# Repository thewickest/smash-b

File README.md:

# Smashboard
Ortholinear bluetooth split keyboard.

Just another split keyboard. Developed with KiKad7.0 and Fusion360.

ZMK configuration in [Smashboard-config](https://github.com/thewickest/smashboard-config)

# Features
- Powered by nice!nano microcontroller
- Compatible with nice!view OLED screen
- Hotswap for MX style Switches
- Different types of cases
- ZMK
- VIA Support
- Bluetooth

# Assembly
Parts needed. I will be linking the parts that I used. Feel free to use other parts, specially for the switches and the hotswap sockets. You can also change the remaining parts but you will have to modify the PCB most probably.
- 2x nice!nano
- 2x nice!view (optional)
- 44x MX Style switches
- 44x Hotswap sockets
- 48x Millmax sockets
- 10x millmax headers sockets
- 2x JST Battery connector (optional)
- 2x Power off/on switch
- 2x Reset button

# Roadmap
- [ ] Hotswap for low profile switches
- [x] Shell case

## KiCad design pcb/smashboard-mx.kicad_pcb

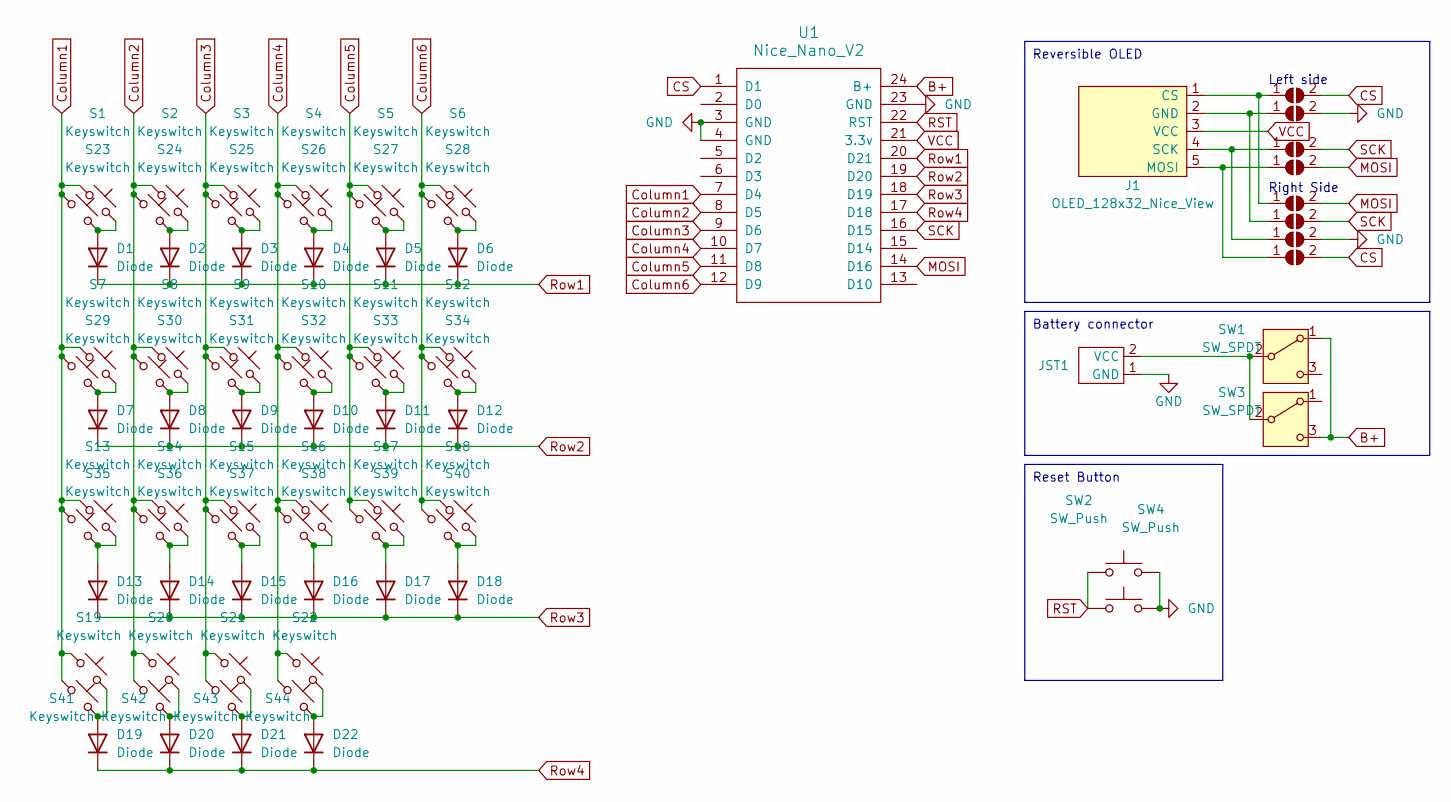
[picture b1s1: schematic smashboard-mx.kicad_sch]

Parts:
D1, D2, D3, D4, D5, D6, D7, D8, D9, D10, D11, D12, D13, D14, D15, D16, D17, D18, D19, D20, D21, D22: Diode; Diode_DO-35
J1: OLED_128x32_Nice_View
JP1, JP2, JP4, JP5, JP6, JP7, JP9, JP10: SolderJumper_2_Open; SolderJumper-2_P1.3mm_Open_TrianglePad1.0x1.5mm
JST1: JST_PH_S2B-PH-K_1x02_P2.00mm_Horizontal
S1, S2, S3, S4, S5, S6, S7, S8, S9, S10, S11, S12, S13, S14, S15, S16, S17, S18, S19, S20, S21, S22, S23, S24, S25, S26, S27, S28, S29, S30, S31, S32, S33, S34, S35, S36, S37, S38, S39, S40, S41, S42, S43, S44: Keyswitch; Hotswap_MX
SW1, SW3: SW_SPDT; SW_SPDT_PCM12
SW2, SW4: SW_Push; Panasonic_EVQPUK_EVQPUB
U1: Nice_Nano_V2

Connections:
B+: SW1.1 (A), SW3.3 (C), U1.24 (B+)
CS: JP1.2 (B), JP10.2 (B), U1.1 (D1)
Column1: S1.1, S7.1, S13.1, S19.1, S23.1, S29.1, S35.1, S41.1, U1.7 (D4)
Column2: S2.1, S8.1, S14.1, S20.1, S24.1, S30.1, S36.1, S42.1, U1.8 (D5)
Column3: S3.1, S9.1, S15.1, S21.1, S25.1, S31.1, S37.1, S43.1, U1.9 (D6)
Column4: S4.1, S10.1, S16.1, S22.1, S26.1, S32.1, S38.1, S44.1, U1.10 (D7)
Column5: S5.1, S11.1, S17.1, S27.1, S33.1, S39.1, U1.11 (D8)
Column6: S6.1, S12.1, S18.1, S28.1, S34.1, S40.1, U1.12 (D9)
GND: JP2.2 (B), JP9.2 (B), JST1.1 (GND), SW2.2, SW4.2, U1.3 (GND), U1.4 (GND), U1.23 (GND)
MOSI: JP5.2 (B), JP6.2 (B), U1.14 (D16)
unnamed: D1.2 (A), S1.2, S23.2
unnamed: D2.2 (A), S2.2, S24.2
unnamed: D3.2 (A), S3.2, S25.2
unnamed: D4.2 (A), S4.2, S26.2
unnamed: D5.2 (A), S5.2, S27.2
unnamed: D6.2 (A), S6.2, S28.2
unnamed: D7.2 (A), S7.2, S29.2
unnamed: D8.2 (A), S8.2, S30.2
unnamed: D9.2 (A), S9.2, S31.2
unnamed: D10.2 (A), S10.2, S32.2
unnamed: D11.2 (A), S11.2, S33.2
unnamed: D12.2 (A), S12.2, S34.2
unnamed: D13.2 (A), S13.2, S35.2
unnamed: D14.2 (A), S14.2, S36.2
unnamed: D15.2 (A), S15.2, S37.2
unnamed: D16.2 (A), S16.2, S38.2
unnamed: D17.2 (A), S17.2, S39.2
unnamed: D18.2 (A), S18.2, S40.2
unnamed: D19.2 (A), S19.2, S41.2
unnamed: D20.2 (A), S20.2, S42.2
unnamed: D21.2 (A), S21.2, S43.2
unnamed: D22.2 (A), S22.2, S44.2
unnamed: J1.1 (CS), JP1.1 (A), JP6.1 (A)
unnamed: J1.2 (GND), JP2.1 (A), JP7.1 (A)
unnamed: J1.5 (MOSI), JP5.1 (A), JP10.1 (A)
unnamed: J1.4 (SCK), JP4.1 (A), JP9.1 (A)
unnamed: JST1.2 (VCC), SW1.2 (B), SW3.2 (B)
RST: SW2.1, SW4.1, U1.22 (RST)
Row1: D1.1 (K), D2.1 (K), D3.1 (K), D4.1 (K), D5.1 (K), D6.1 (K), U1.20 (D21)
Row2: D7.1 (K), D8.1 (K), D9.1 (K), D10.1 (K), D11.1 (K), D12.1 (K), U1.19 (D20)
Row3: D13.1 (K), D14.1 (K), D15.1 (K), D16.1 (K), D17.1 (K), D18.1 (K), U1.18 (D19)
Row4: D19.1 (K), D20.1 (K), D21.1 (K), D22.1 (K), U1.17 (D18)
SCK: JP4.2 (B), JP7.2 (B), U1.16 (D15)
VCC: J1.3 (VCC), U1.21 (3.3v)

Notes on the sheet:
Reset Button
Reversible OLED
Battery connector
Left side
Right Side

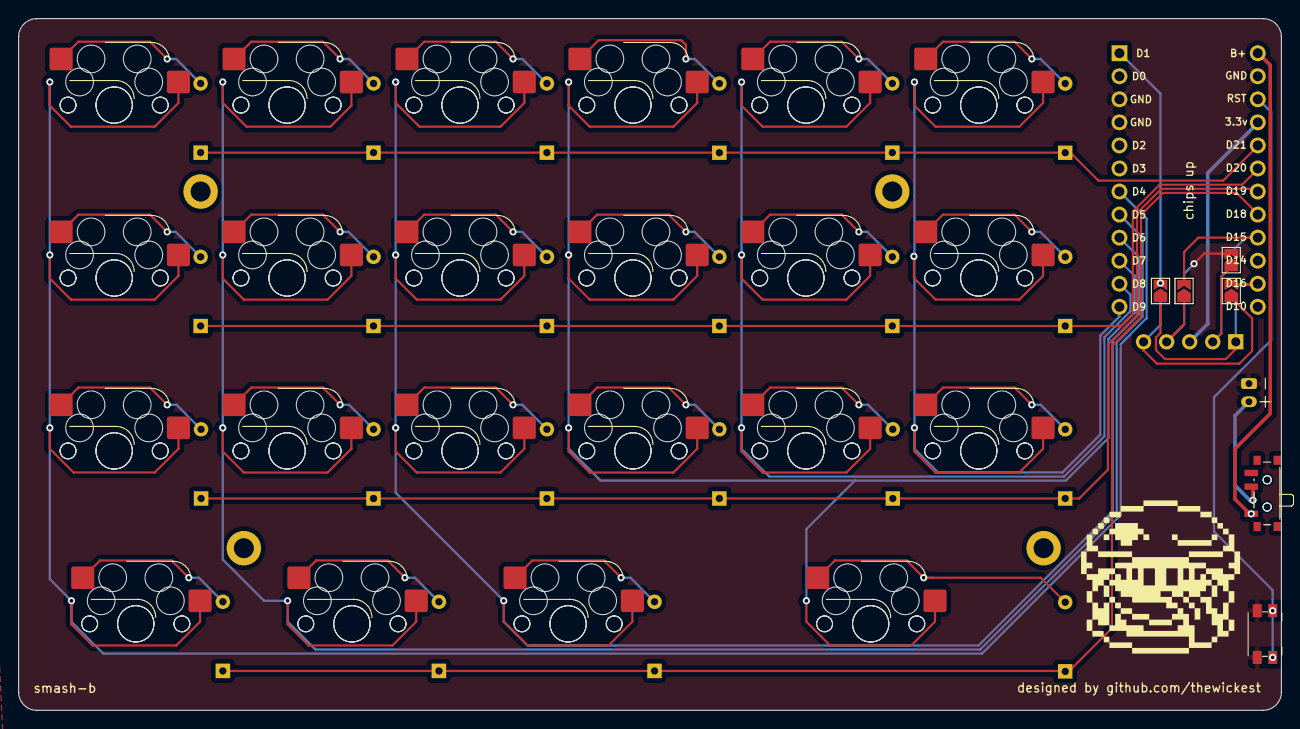
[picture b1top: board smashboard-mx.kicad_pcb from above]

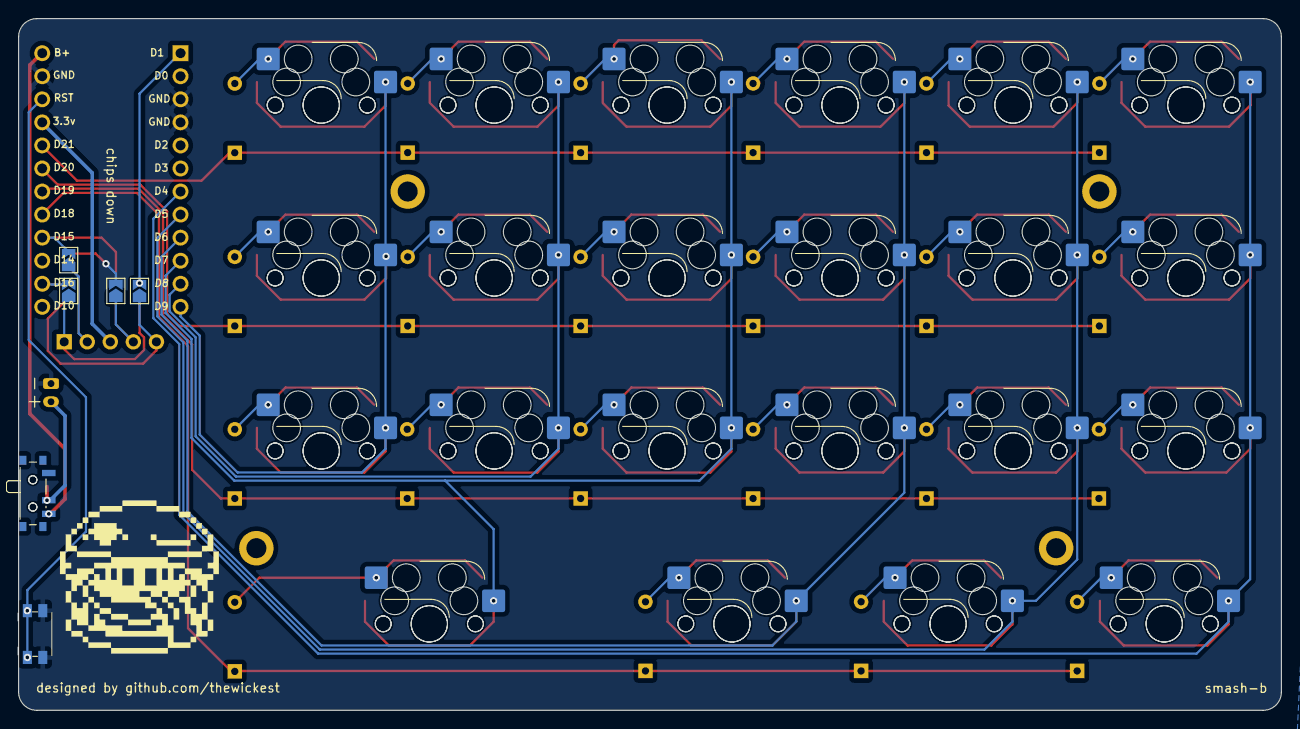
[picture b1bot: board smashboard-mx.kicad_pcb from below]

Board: 2 copper layers, 139.1 x 76.2 mm, 81 parts (50 on the bottom side), 44 nets.

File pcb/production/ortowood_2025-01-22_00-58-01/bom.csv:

Designator,Footprint,Quantity,Value,LCSC Part #
"D1, D10, D11, D12, D13, D14, D15, D16, D17, D18, D19, D2, D20, D21, D22, D3, D4, D5, D6, D7, D8, D9",Diode_DO-35,22,Diode,
"S1, S10, S11, S12, S13, S14, S15, S16, S17, S18, S2, S23, S24, S25, S26, S27, S28, S29, S3, S30, S31, S32, S33, S34, S35, S36, S37, S38, S39, S4, S40, S5, S6, S7, S8, S9",Hotswap_Choc_V1V2_1.00u,36,Keyswitch,
"S19, S20, S21, S41, S42, S43",Hotswap_Choc_V1V2_1.25u,6,Keyswitch,
"S22, S44",Hotswap_Choc_V1V2_2.25u,2,Keyswitch,
U1,Nice_Nano_V2,1,Nice_Nano_V2,

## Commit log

2025-01-24 Initial Smash Board
2025-01-25 PCB: Reset button, on/off button and some modification in the vias
2025-01-25 Modified reset and on/off buttons footprints
2025-01-25 Some errors after changing the switch footprint
2025-01-29 PCB for MX and Kailh switches
2025-02-03 Add M2 holes into the PCB
2025-02-03 Move reset button
2025-02-03 feat: black & white logos
    transparent background, 32x32px
2025-02-04 Add Logo and name
2025-02-04 Production files
2025-02-09 New Case - notoppings
2025-02-09 Gitignore
2025-02-09 Remove backups
2025-02-09 Reorder folders
2025-02-10 The Classic case
2025-02-10 The Barebones case
2025-02-11 Organize folders
2025-02-15 Two patties case
2025-02-15 PCB image
2025-02-18 Move 2u diode to the side. Interference with the stab
2025-04-10 Finished v1.0
